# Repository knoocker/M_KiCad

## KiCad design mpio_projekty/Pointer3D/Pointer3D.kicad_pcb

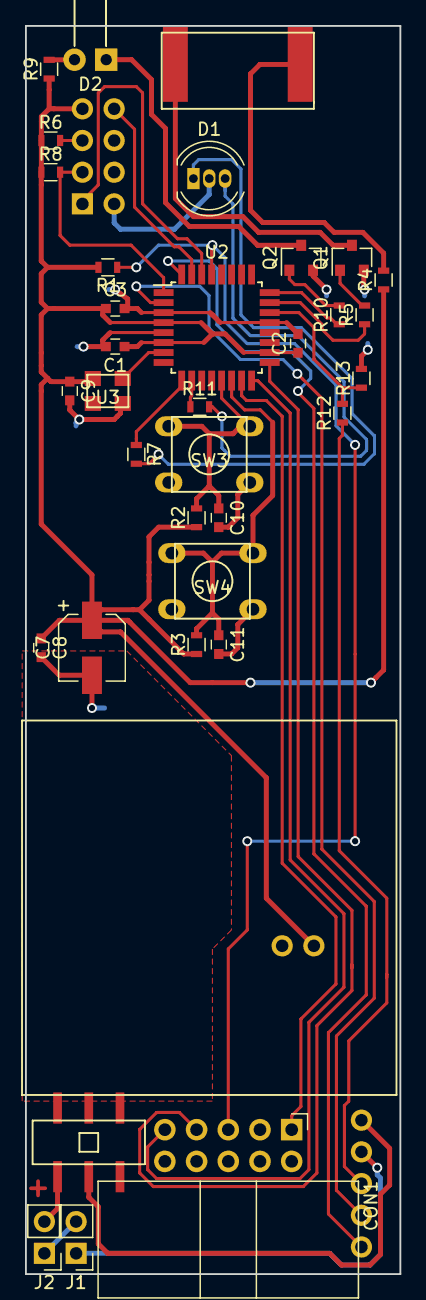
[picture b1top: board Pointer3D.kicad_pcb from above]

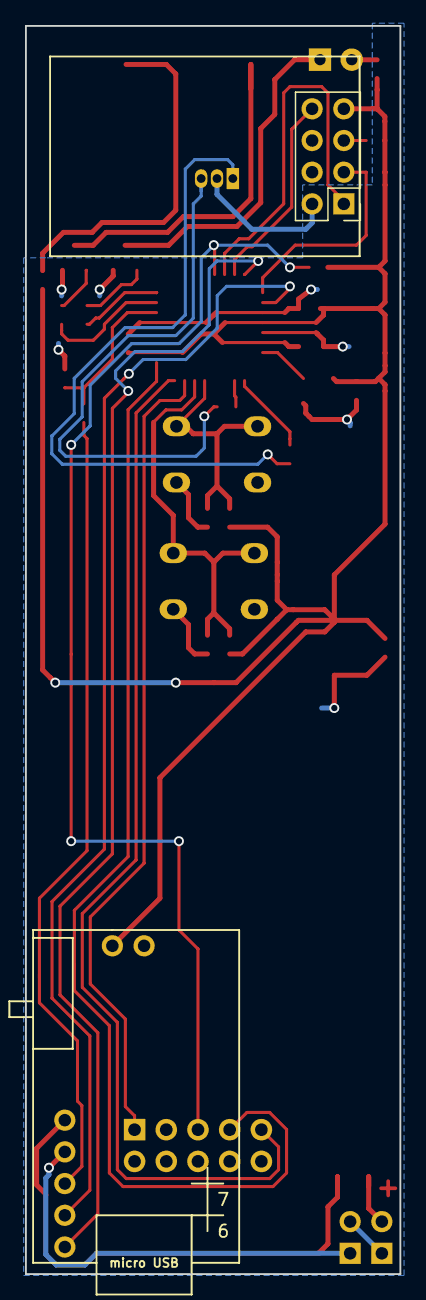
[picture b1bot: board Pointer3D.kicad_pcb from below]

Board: 2 copper layers, 30.0 x 100.0 mm, 37 parts (2 on the bottom side), 33 nets.

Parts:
BT1: Bat_cel; szescian_30x30x6
BZ1: Buzzer; piezo45_10mm
C1, C2, C3, C8, C9, C10, C11: 100n; C_0603
C7: 22u; CP_Elec_5x4.5
CON1: AVR-ISP-10; IDC10_45
D1: LED_Dual_AAC; LED_D5.0mm-3-1.27pitch
D2: LED; LED_D3.0mm_Horizontal_O6.35mm_Z10.0mm
J1: BATTERY; Pin_Header_Straight_1x02_Pitch2.54mm
J2: I_meas; Pin_Header_Straight_1x02_Pitch2.54mm
Q1, Q2: BC817; SOT-23
R1, R2, R3, R6, R8, R10, R12, R13: 10K; R_0603
R4: 0R; R_0603
R5: 1K2; R_0603
R7: 1K5; R_0603
R9: 47R; R_0603
R11: 560R; R_0603
SW1: SW_DIP_x01; MSS-2235S
SW3, SW4: SW_Push; TACT-69K-F_4.5x6.5mm
U1: digi_lion; digi_lion_no_D+D-
U2: ATMEGA48A-AU; TQFP-32_7x7mm_Pitch0.8mm
U3: 12.8MHz; crystal_3.2x2.5
U4: ESP8266

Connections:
+3V3: C1.1, C2.1, C3.1, C7.1, C8.1, C9.1, R1.2, R2.1, R3.1, R4.1, R6.1, R8.1, R9.1, U1.9, U2.4, U2.6, U2.18, U3.4, U4.4
DIGI_IRQ_INT: U1.1, U2.32
DIGI_TX: U1.2, U2.2
ESP_PD: R8.2, U2.1, U4.2
ESP_RX: U2.31, U4.5
ESP_TX: U2.30, U4.1
GND: C1.2, C2.2, C3.2, C7.2, C8.2, C9.2, C10.2, C11.2, CON1.4, CON1.6, CON1.8, CON1.10, D1.3, Q1.2, Q2.2, R13.2, SW3.2, SW4.2, U1.8, U2.3, U2.5, U2.21, U3.2, U4.8
IR: R10.1, U2.24
LADOWANIE: R12.2, R13.1, U2.22
LED_GREEN: R11.1, U2.10
LED_RED: R7.1, U2.9
MISO: CON1.9, U2.16
MOSI: CON1.1, U2.15
unnamed: BZ1.1, R4.2
unnamed: BZ1.2, Q1.3
unnamed: D1.1, R7.2
unnamed: D1.2, R11.2
unnamed: D2.1, Q2.3
unnamed: D2.2, R9.2
unnamed: J1.1, U1.4
unnamed: J1.2, J2.1
unnamed: J2.2, SW1.1
unnamed: Q1.1, R5.2
unnamed: Q2.1, R10.2
unnamed: R6.2, U4.3
unnamed: R12.1, U1.3
unnamed: SW1.2, U1.5
RESET: CON1.5, R1.1, U2.29
SCK: CON1.7, U2.17
SW1: C10.1, R2.2, SW3.1, U2.13
SW2: C11.1, R3.2, SW4.1, U2.14
TCXO: U2.7, U3.3
US: R5.1, U2.23

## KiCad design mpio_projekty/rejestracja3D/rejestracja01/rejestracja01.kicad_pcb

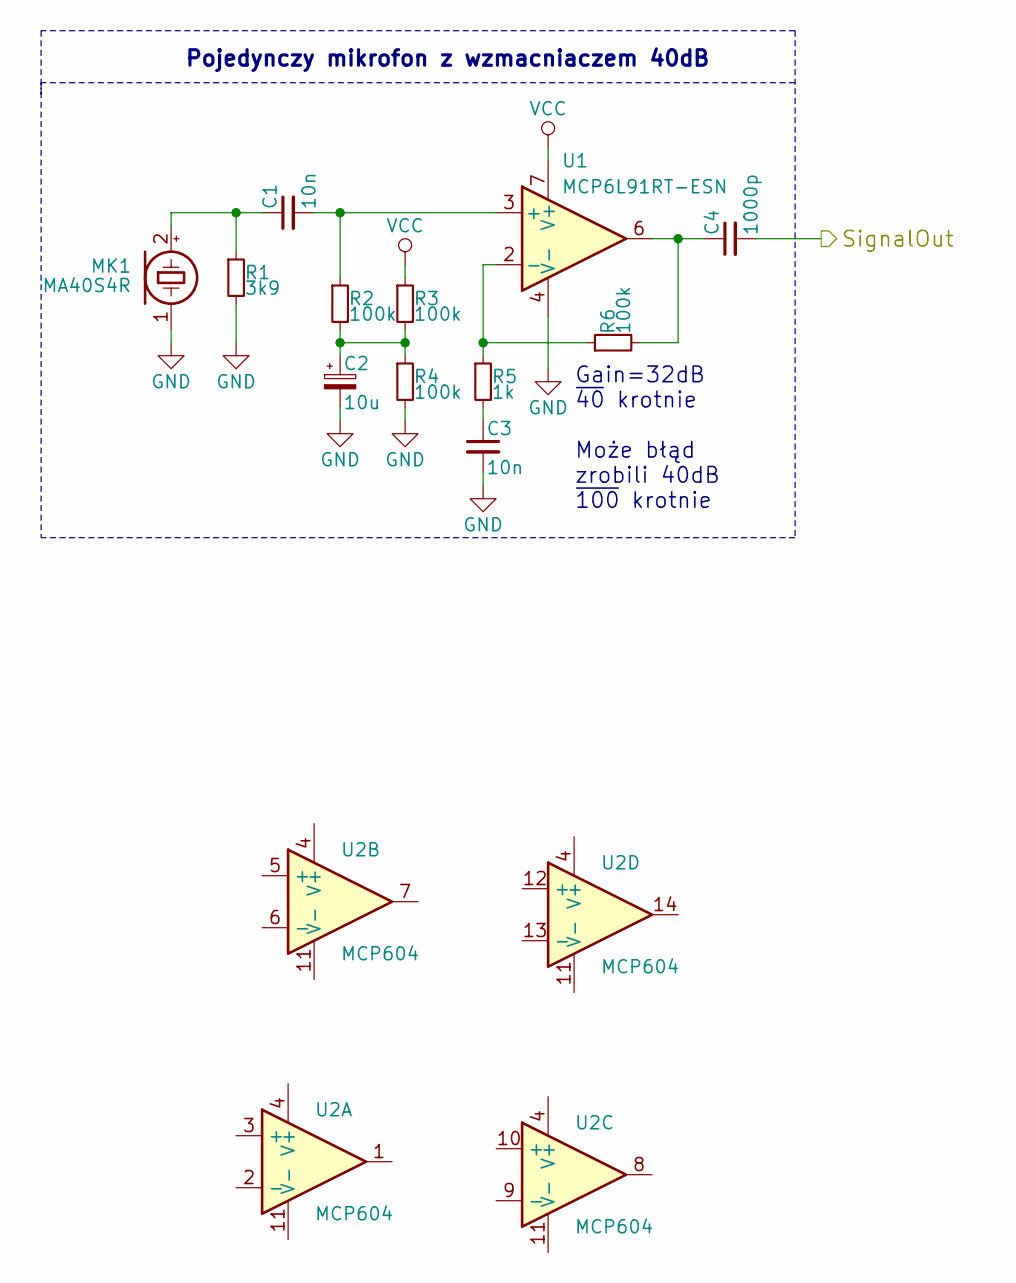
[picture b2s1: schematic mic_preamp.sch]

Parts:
C1, C3: 10n; C_0603
C2: 10u; CP_Elec_5x5.3
C4: 1000p; C_0603
MK1: MA40S4R; MA40S4S_straight
R1: 3k9; R_0603
R2, R3, R4, R6: 100k; R_0603
R5: 1k; R_0603
U1: MCP6L91RT-ESN; SOIC-8_3.9x4.9mm_Pitch1.27mm
U2: MCP604; TSSOP-14_4.4x5mm_Pitch0.65mm

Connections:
/mic_preamp_a/SignalOut: C4.2; also elsewhere on the board
GND: C2.2, C3.2, MK1.1 (-), R1.2, R4.2, U1.4 (V-); also elsewhere on the board
unnamed: C1.1, MK1.2 (+), R1.1
unnamed: C1.2, R2.1, U1.3 (+)
unnamed: C2.1, R2.2, R3.2, R4.1
unnamed: C3.1, R5.2
unnamed: C4.1, R6.2, U1.6
unnamed: R5.1, R6.1, U1.2 (-)
VCC: R3.1, U1.7 (V+); also elsewhere on the board

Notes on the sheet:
Gain=32dB ~40 krotnie Może błąd zrobili 40dB ~100 krotnie
Pojedynczy mikrofon z wzmacniaczem 40dB

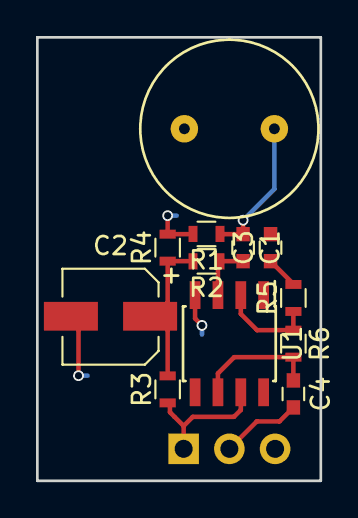
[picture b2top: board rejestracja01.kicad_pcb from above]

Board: 2 copper layers, 15.7 x 24.6 mm, 13 parts (1 on the bottom side), 9 nets.

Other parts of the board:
J1: Conn_01x03; Pin_Header_Straight_1x03_Pitch2.54mm

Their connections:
/mic_preamp_a/SignalOut: J1.2; also elsewhere on the board
GND: J1.3; also elsewhere on the board
VCC: J1.1; also elsewhere on the board

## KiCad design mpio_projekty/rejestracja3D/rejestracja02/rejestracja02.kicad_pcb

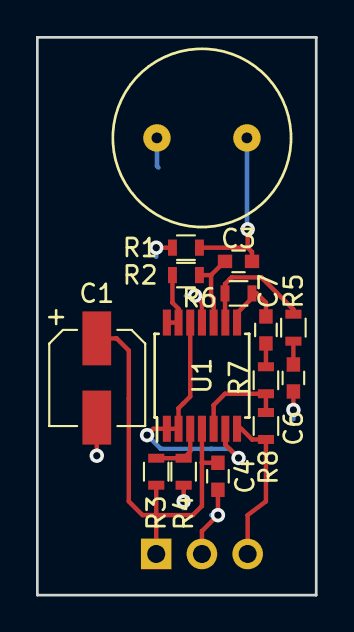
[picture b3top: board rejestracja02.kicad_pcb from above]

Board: 2 copper layers, 15.5 x 31.0 mm, 16 parts (1 on the bottom side), 13 nets.

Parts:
C1: 10u; CP_Elec_5x5.3
C3, C6: 10n; C_0603
C4: 0,1u; C_0603
C7: 1000p; C_0603
J1: Conn_01x03; Pin_Header_Straight_1x03_Pitch2.54mm
MK1: MA40S4R; MA40S4S_straight
R1: 3K9; R_0603
R2, R6: 100K; R_0603
R3, R4: 10K; R_0603
R5, R7: 1K; R_0603
R8: 33K; R_0603
U1: MCP604; TSSOP-14_4.4x5mm_Pitch0.65mm

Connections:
+3V3: C1.1, C4.1, J1.1, R3.2, U1.4
/Vref1: U1.1, U1.2, U1.6, U1.12
/Vref2: R2.1, U1.13, U1.14
/comp: J1.3, R8.2, U1.7
/preamp: C7.2, R7.1
GNDA: C1.2, C4.2, C6.2, J1.2, MK1.1, R1.1, R4.1, U1.11
unnamed: C3.1, MK1.2, R1.2
unnamed: C3.2, R2.2, U1.10
unnamed: C6.1, R5.1
unnamed: C7.1, R6.2, U1.8
unnamed: R3.1, R4.2, U1.3
unnamed: R5.2, R6.1, U1.9
unnamed: R7.2, R8.1, U1.5

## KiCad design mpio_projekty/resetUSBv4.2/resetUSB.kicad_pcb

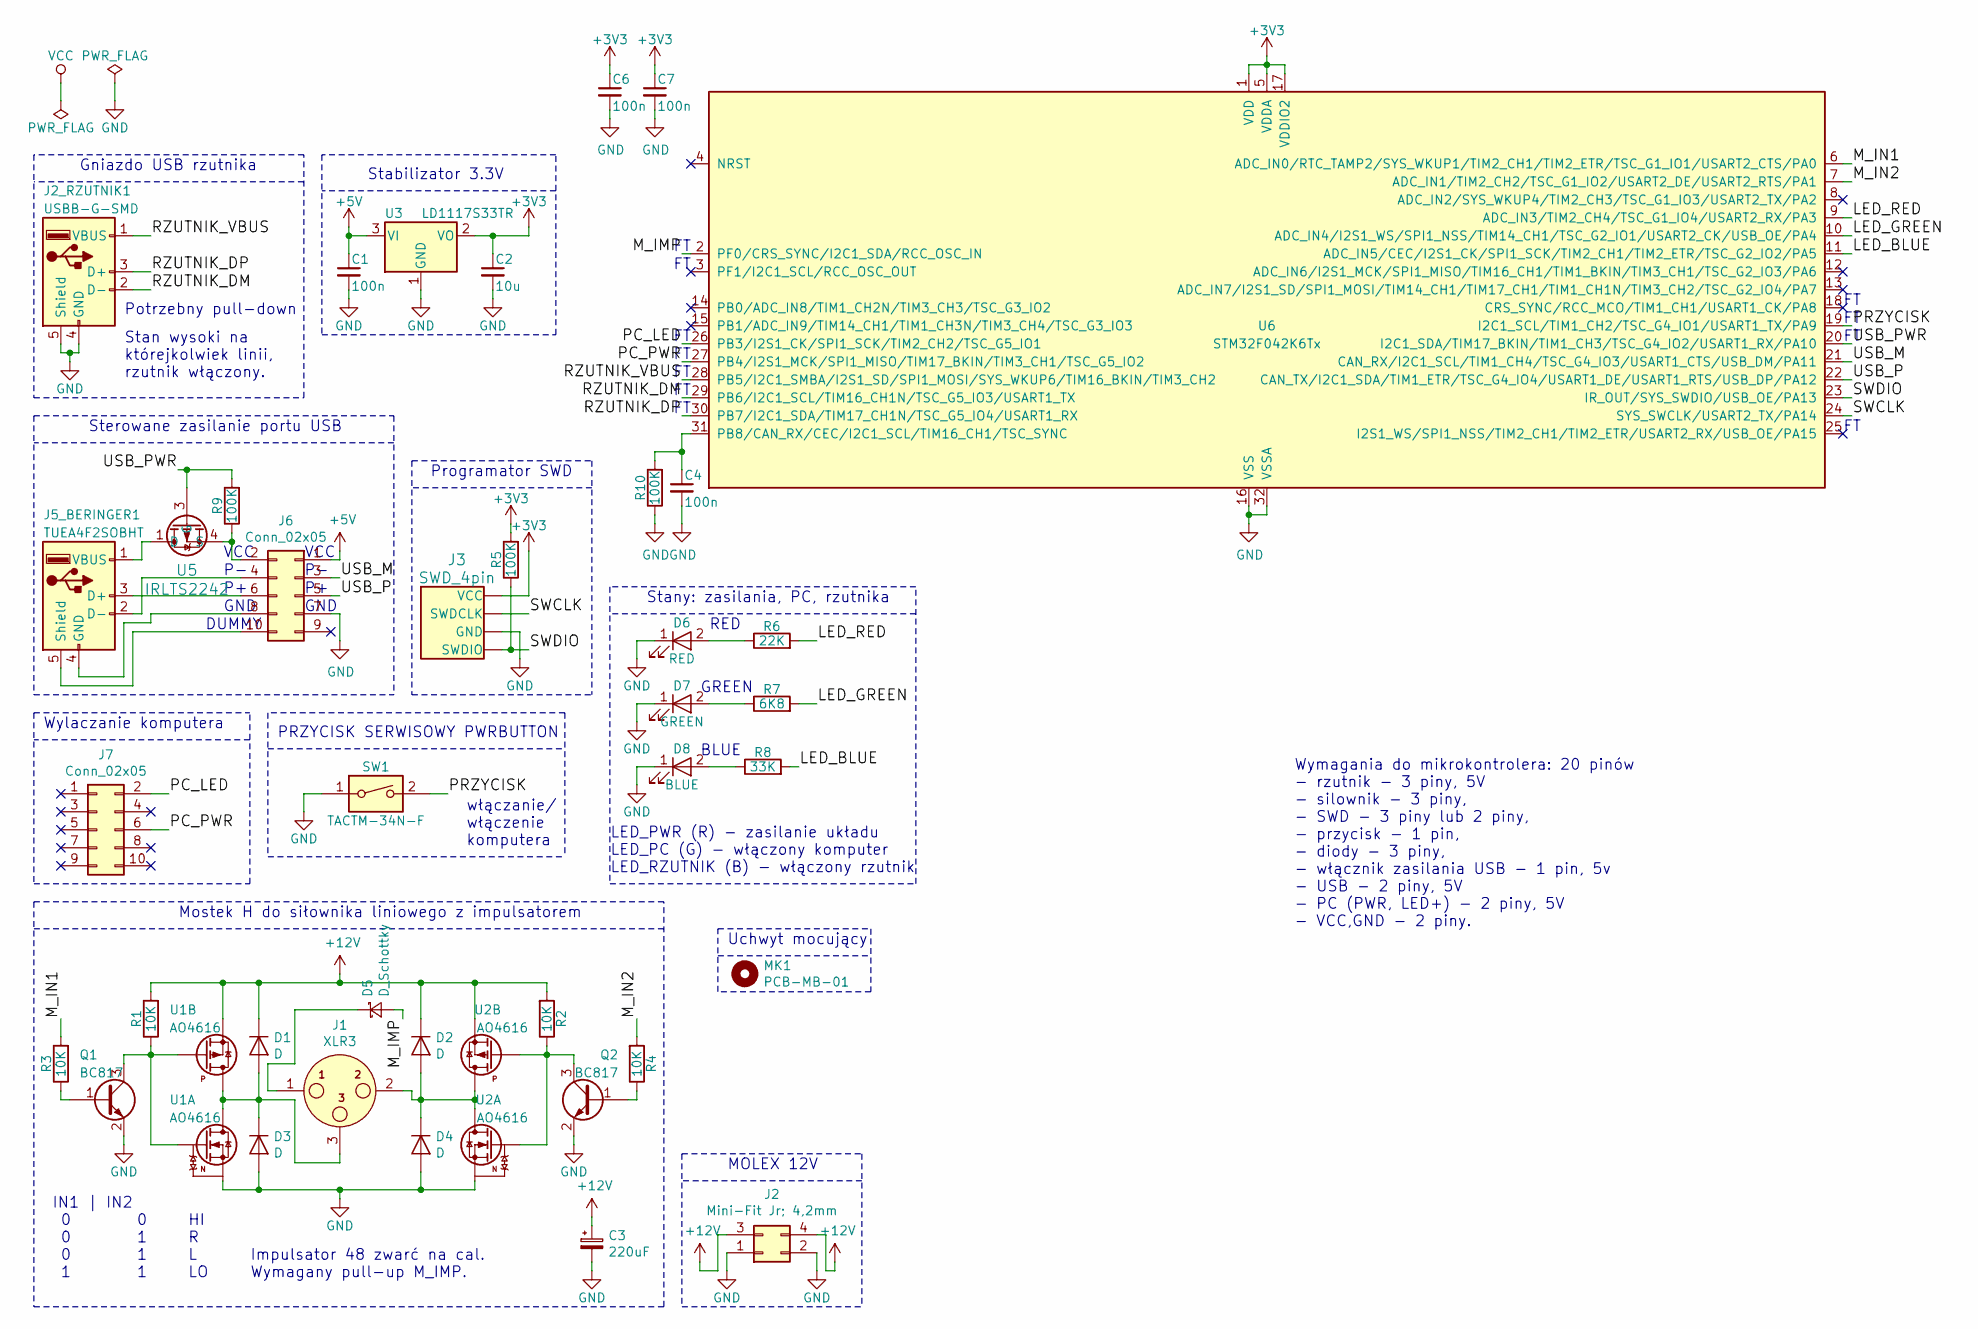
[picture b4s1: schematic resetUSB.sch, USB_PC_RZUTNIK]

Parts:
C1, C4, C6, C7: 100n; C_0603
C2: 10u; CP_Elec_5x5.3
C3: 220uF; CP_Elec_8x10
D1, D2, D3, D4: D; D_SMA
D5: D_Schottky; D_SOD-523
D6: RED; LED_0603
D7: GREEN; LED_0603
D8: BLUE; LED_0603
J1: XLR3; AC3MAH-AU-PRE
J2: Mini-Fit Jr; 4,2mm; Molex_MiniFit-JR-5556-04A_2x02x4.20mm_Straight
J2_RZUTNIK1: USBB-G-SMD; USB-B_SMD
J3: SWD_4pin; Pin_Header_Straight_1x04_Pitch2.54mm
J5_BERINGER1: TUEA4F2SOBHT; USB-A_SMD
J6, J7: Conn_02x05; IDC10
MK1: PCB-MB-01
Q1, Q2: BC817; SOT-23
R1, R2, R3, R4: 10K; R_0603
R5, R9, R10: 100K; R_0603
R6: 22K; R_0603
R7: 6K8; R_0603
R8: 33K; R_0603
SW1: TACTM-34N-F; SW_3x6_1,6x7,4
U1, U2: AO4616; SOIC-8_3.9x4.9mm_Pitch1.27mm
U3: LD1117S33TR; SOT-223-3_TabPin2
U5: IRLTS2242; TSOP-6_1.65x3.05mm_Pitch0.95mm
U6: STM32F042K6Tx; LQFP-32_5x5mm_Pitch0.5mm

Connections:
+3V3: C2.1, C6.1, C7.1, J3.1 (VCC), R5.2, U3.2 (VO), U6.1 (VDD), U6.5 (VDDA), U6.17 (VDDIO2)
+5V: C1.1, J6.1, U3.3 (VI)
+12V: C3.1, D1.1 (K), D2.1 (K), J2.3, J2.4, R1.2, R2.2, U1.3 (S), U2.3 (S)
/LED_BLUE: R8.2, U6.11 (ADC_IN5/CEC/I2S1_CK/SPI1_SCK/TIM2_CH1/T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)
/LED_GREEN: R7.2, U6.10 (ADC_IN4/I2S1_WS/SPI1_NSS/TIM14_CH1/TSC_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)
/LED_RED: R6.2, U6.9 (ADC_IN3/TIM2_CH4/TSC_G1_IO4/USART2_RX/P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)
/M_IMP: D5.2 (A), U6.2 (PF0/CRS_SYNC/I2C1_SDA/RCC_OSC_IN)
/M_IN1: R3.2, U6.6 (ADC_IN0/RTC_TAMP2/SYS_WKUP1/TIM2_CH1/TI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)
/M_IN2: R4.2, U6.7 (ADC_IN1/TIM2_CH2/TSC_G1_IO2/USART2_DE/U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)
/PC_LED: J7.2, U6.26 (PB3/I2S1_CK/SPI1_SCK/TIM2_CH2/TSC_G5_IO1)
/PC_PWR: J7.6, U6.27 (PB4/I2S1_MCK/SPI1_MISO/TIM17_BKIN/TIM3_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)
/PRZYCISK: SW1.2, U6.19 (I2C1_SCL/TIM1_CH2/TSC_G4_IO1/USART1_TX/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)
/RZUTNIK_DM: J2_RZUTNIK1.2 (D-), U6.29 (PB6/I2C1_SCL/TIM16_CH1N/TSC_G5_IO3/USAR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)
/RZUTNIK_DP: J2_RZUTNIK1.3 (D+), U6.30 (PB7/I2C1_SDA/TIM17_CH1N/TSC_G5_IO4/USAR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)
/RZUTNIK_VBUS: J2_RZUTNIK1.1 (VBUS), U6.28 (PB5/I2C1_SMBA/I2S1_SD/SPI1_MOSI/SYS_WKU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)
/SWCLK: J3.2 (SWDCLK), U6.24 (SYS_SWCLK/USART2_TX/PA14)
/SWDIO: J3.4 (SWDIO), R5.1, U6.23 (IR_OUT/SYS_SWDIO/USB_OE/PA13)
/USB_M: J6.3, U6.21 (CAN_RX/I2C1_SCL/TIM1_CH4/TSC_G4_IO3/USA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)
/USB_P: J6.5, U6.22 (CAN_TX/I2C1_SDA/TIM1_ETR/TSC_G4_IO4/USA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)
/USB_PWR: R9.2, U5.3 (G), U6.20 (I2C1_SDA/TIM17_BKIN/TIM1_CH3/TSC_G4_IO2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)
GND: C1.2, C2.2, C3.2, C4.2, C6.2, C7.2, D3.2 (A), D4.2 (A), D6.1 (K), D7.1 (K), D8.1 (K), J2.1, J2.2, J2_RZUTNIK1.4 (GND), J2_RZUTNIK1.5 (Shield), J3.3 (GND), J6.7, Q1.2 (E), Q2.2 (E), R10.1, SW1.1, U1.1 (S), U2.1 (S), U3.1 (GND), U6.16 (VSS), U6.32 (VSSA)
unnamed: C4.1, R10.2, U6.31 (PB8/CAN_RX/CEC/I2C1_SCL/TIM16_CH1/TSC_S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)
unnamed: D1.2 (A), D3.1 (K), J1.3, U1.5 (D), U1.6 (D), U1.7 (D), U1.8 (D)
unnamed: D2.2 (A), D4.1 (K), J1.2, U2.5 (D), U2.6 (D), U2.7 (D), U2.8 (D)
unnamed: D5.1 (K), J1.1
unnamed: D6.2 (A), R6.1
unnamed: D7.2 (A), R7.1
unnamed: D8.2 (A), R8.1
unnamed: J5_BERINGER1.1 (VBUS), U5.1 (D), U5.2 (D), U5.5 (D), U5.6 (D)
unnamed: J5_BERINGER1.2 (D-), J6.4
unnamed: J5_BERINGER1.3 (D+), J6.6
unnamed: J5_BERINGER1.4 (GND), J6.8
unnamed: J5_BERINGER1.5 (Shield), J6.10
unnamed: J6.2, R9.1, U5.4 (S)
unnamed: Q1.1 (B), R3.1
unnamed: Q1.3 (C), R1.1, U1.2 (G), U1.4 (G)
unnamed: Q2.1 (B), R4.1
unnamed: Q2.3 (C), R2.1, U2.2 (G), U2.4 (G)

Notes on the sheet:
Gniazdo USB rzutnika
Stan wysoki na którejkolwiek linii, rzutnik włączony.
PRZYCISK SERWISOWY PWRBUTTON
Stany: zasilania, PC, rzutnika
włączanie/ włączenie komputera
LED_PWR (R) - zasilanie układu LED_PC (G) - włączony komputer LED_RZUTNIK (B) - włączony rzutnik
Wymagania do mikrokontrolera: 20 pinów - rzutnik - 3 piny, 5V - silownik - 3 piny, - SWD - 3 piny lub 2 piny, - przycisk - 1 pin, - diody - 3 piny, - włącznik zasilania USB - 1 pin, 5v - USB - 2 piny, 5V - PC (PWR, LED+) - 2 piny, 5V - VCC,GND - 2 piny.
RED
GREEN
BLUE
VCC
GND
DUMMY
Sterowane zasilanie portu USB
Wylaczanie komputera
Programator SWD
Mostek H do siłownika liniowego z impulsatorem
Impulsator 48 zwarć na cal. Wymagany pull-up M_IMP.
Stabilizator 3.3V
Potrzebny pull-down
IN1 | IN2 0 0 HI 0 1 R 0 1 L 1 1 LO
MOLEX 12V
Uchwyt mocujący

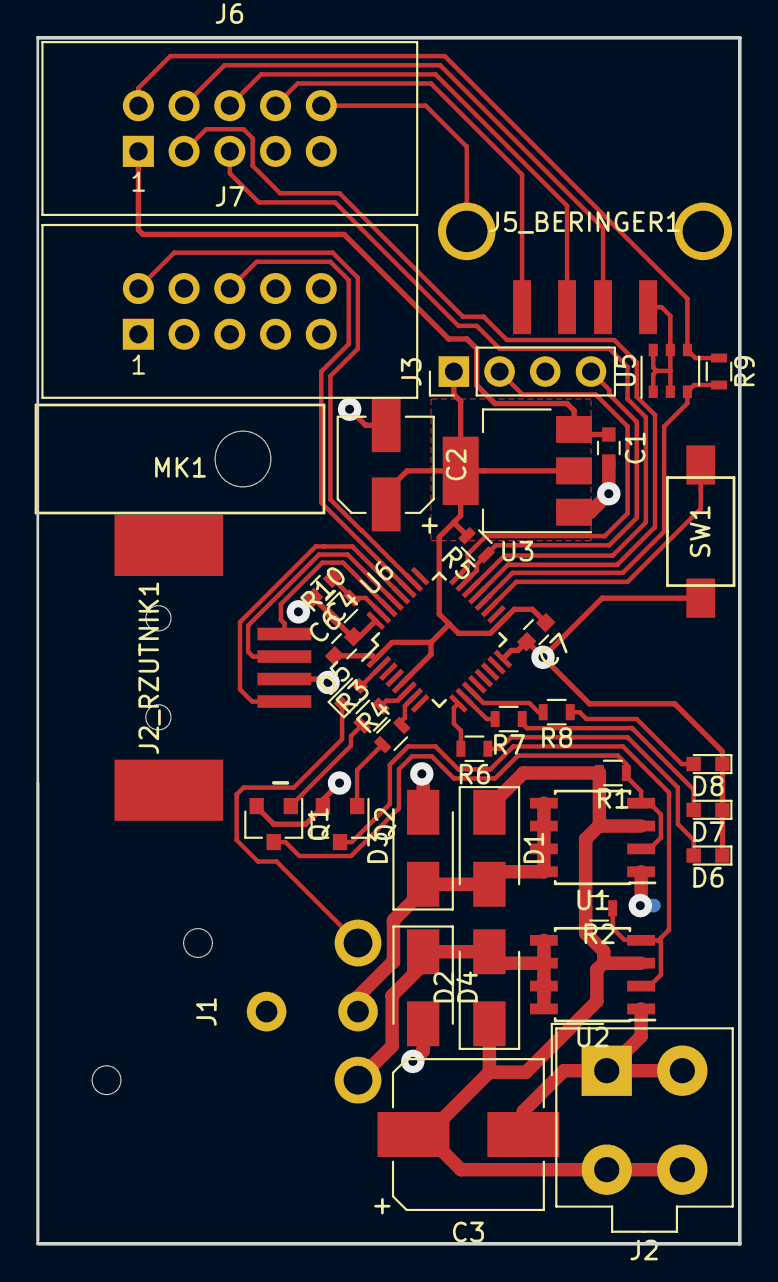
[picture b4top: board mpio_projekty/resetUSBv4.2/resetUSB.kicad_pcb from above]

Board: 2 copper layers, 39.0 x 67.0 mm, 40 parts (0 on the bottom side), 38 nets.

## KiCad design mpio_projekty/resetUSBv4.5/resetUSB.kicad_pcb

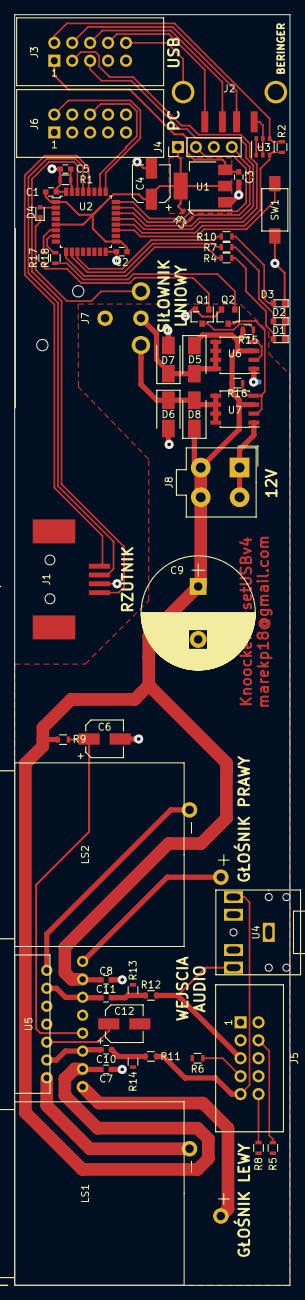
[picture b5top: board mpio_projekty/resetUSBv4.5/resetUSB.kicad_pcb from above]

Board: 2 copper layers, 39.0 x 180.0 mm, 58 parts (0 on the bottom side), 54 nets.

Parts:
C1, C2, C3, C5, C7, C8: 100n; C_0603
C4, C6: 10u; CP_Elec_5x5.3
C9: 4700u; CP_Radial_D16.0mm_P7.50mm
C10, C11: 0.47u; C_0603
C12: 47u; CP_Elec_5x5.3
D1: RED; LED_0603
D2: GREEN; LED_0603
D3: BLUE; LED_0603
D4: D_Schottky; D_SOD-523
D5, D6, D7, D8: D; D_SMA
J1: USBB-G-SMD; USB-B_SMD
J2: TUEA4F2SOBHT; USB-A_SMD
J3, J5, J6: Conn_02x05; IDC10
J4: SWD_4pin; Pin_Header_Straight_1x04_Pitch2.54mm
J7: XLR3; AC3MAH-AU-PRE
J8: Mini-Fit Jr; 4,2mm; Molex_MiniFit-JR-5556-04A_2x02x4.20mm_Straight
LS1, LS2: speak-on; NLJ2MD-H
Q1, Q2: BC817; SOT-23
R1, R2, R3: 100K; R_0603
R4: 22K; R_0603
R5, R6, R8: N.C.; R_0603
R7: 6K8; R_0603
R9: 47K; R_0603
R10: 33K; R_0603
R11, R12: 4K7; R_0603
R13, R14, R15, R16, R17, R18: 10K; R_0603
SW1: TACTM-34N-F; SW_3x6_1,6x7,4
U1: LD1117S33TR; SOT-223-3_TabPin2
U2: STM32F042K6Tx; LQFP-32_7x7mm_Pitch0.8mm
U3: IRLTS2242; TSOP-6_1.65x3.05mm_Pitch0.95mm
U4: JC-128
U5: TDA7375; MULTIWATT15
U6, U7: AO4616; SOIC-8_3.9x4.9mm_Pitch1.27mm

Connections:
+3V3: C1.1, C2.1, C4.1, J4.1, R3.2, U1.2, U2.1, U2.5, U2.17
+5V: C3.1, J3.1, U1.3
+12V: C7.1, C8.1, C9.1, D5.1, D6.1, J8.3, J8.4, R9.1, R15.2, R16.2, U5.3, U5.13, U6.3, U7.3
/LED_BLUE: R10.2, U2.11
/LED_GREEN: R7.2, U2.10
/LED_RED: R4.2, U2.9
/M_IMP: D4.2, U2.2
/M_IN1: R17.2, U2.6
/M_IN2: R18.2, U2.7
/OUT2_L: J5.9, R11.1, U4.2
/OUT2_R: J5.5, R12.1, U4.5
/PC_LED: J6.2, U2.25
/PC_PWR: J6.6, U2.26
/PRZYCISK: SW1.2, U2.19
/RZUTNIK_DM: J1.2, U2.29
/RZUTNIK_DP: J1.3, U2.28
/RZUTNIK_VBUS: J1.1, U2.30
/SWCLK: J4.2, U2.24
/SWDIO: J4.4, R3.1, U2.23
/USB_M: J3.3, U2.21
/USB_P: J3.5, U2.22
/USB_PWR: R2.2, U2.20, U3.3
GND: C1.2, C2.2, C3.2, C4.2, C5.2, D1.1, D2.1, D3.1, J1.4, J1.5, J3.7, J4.3, R1.1, SW1.1, U1.1, U2.16, U2.32
GNDA: C6.2, C7.2, C8.2, C9.2, C12.2, D7.2, D8.2, J5.2, J8.1, J8.2, Q1.2, Q2.2, R5.2, R6.1, R8.2, R13.2, R14.2, U4.1, U5.8, U5.9, U6.1, U7.1
unnamed: C5.1, R1.2, U2.31
unnamed: C6.1, R9.2, U5.7
unnamed: C10.1, R11.2, R14.1
unnamed: C10.2, U5.4, U5.5
unnamed: C11.1, R12.2, R13.1
unnamed: C11.2, U5.11, U5.12
unnamed: C12.1, U5.6
unnamed: D1.2, R4.1
unnamed: D2.2, R7.1
unnamed: D3.2, R10.1
unnamed: D4.1, J7.1
unnamed: D5.2, D7.1, J7.3, U6.5, U6.6, U6.7, U6.8
unnamed: D6.2, D8.1, J7.2, U7.5, U7.6, U7.7, U7.8
unnamed: J2.1, U3.1, U3.2, U3.5, U3.6
unnamed: J2.2, J3.4
unnamed: J2.3, J3.6
unnamed: J2.4, J3.8
unnamed: J2.5, J3.10
unnamed: J3.2, R2.1, U3.4
unnamed: J5.4, R5.1
unnamed: J5.7, R6.2
unnamed: J5.10, R8.1
unnamed: LS1.1, U5.1
unnamed: LS1.2, U5.2
unnamed: LS2.1, U5.15
unnamed: LS2.2, U5.14
unnamed: Q1.1, R17.1
unnamed: Q1.3, R15.1, U6.2, U6.4
unnamed: Q2.1, R18.1
unnamed: Q2.3, R16.1, U7.2, U7.4
